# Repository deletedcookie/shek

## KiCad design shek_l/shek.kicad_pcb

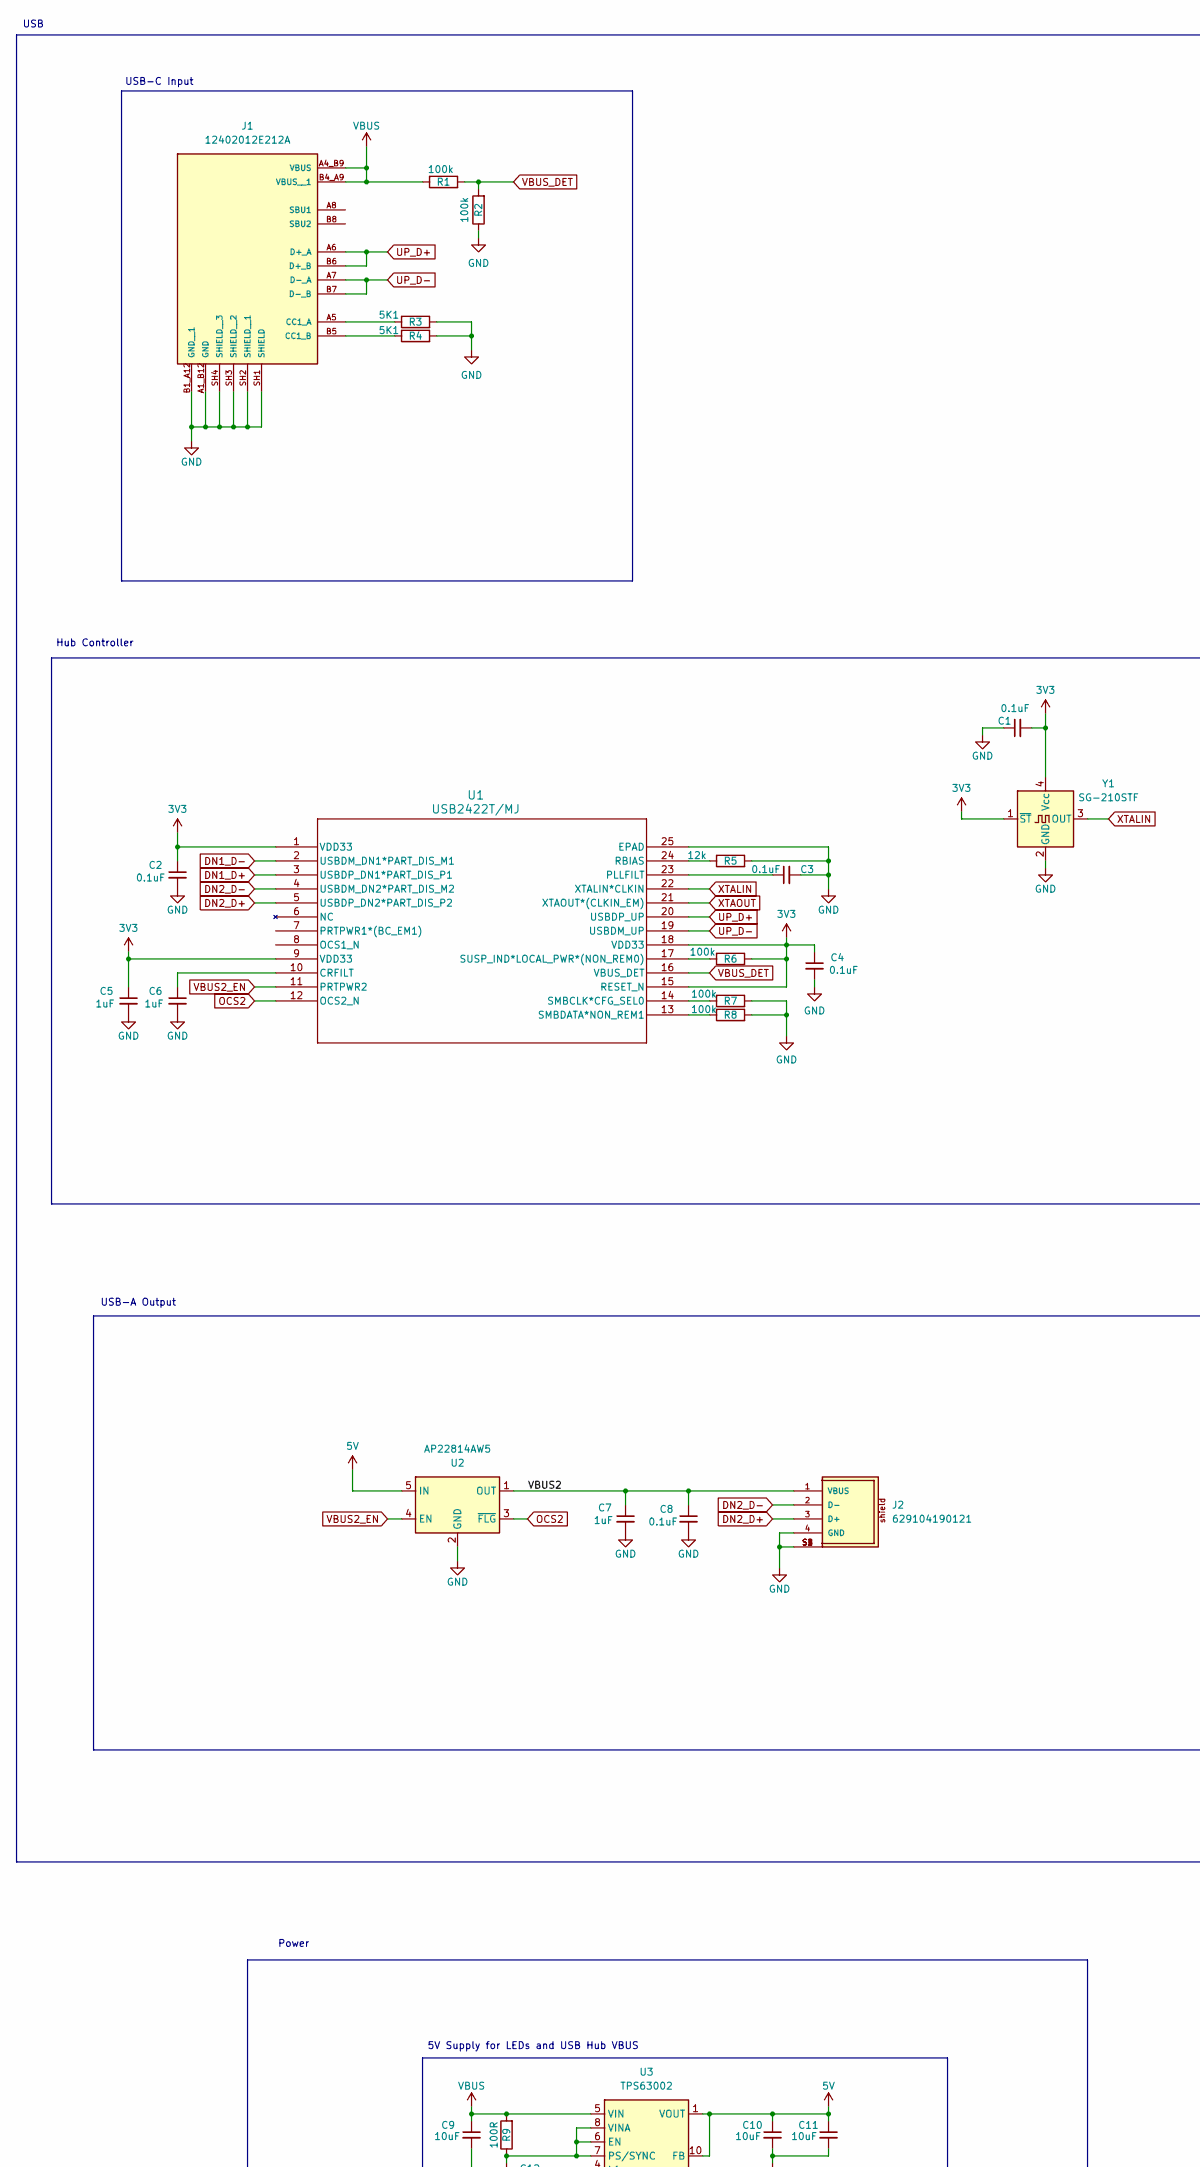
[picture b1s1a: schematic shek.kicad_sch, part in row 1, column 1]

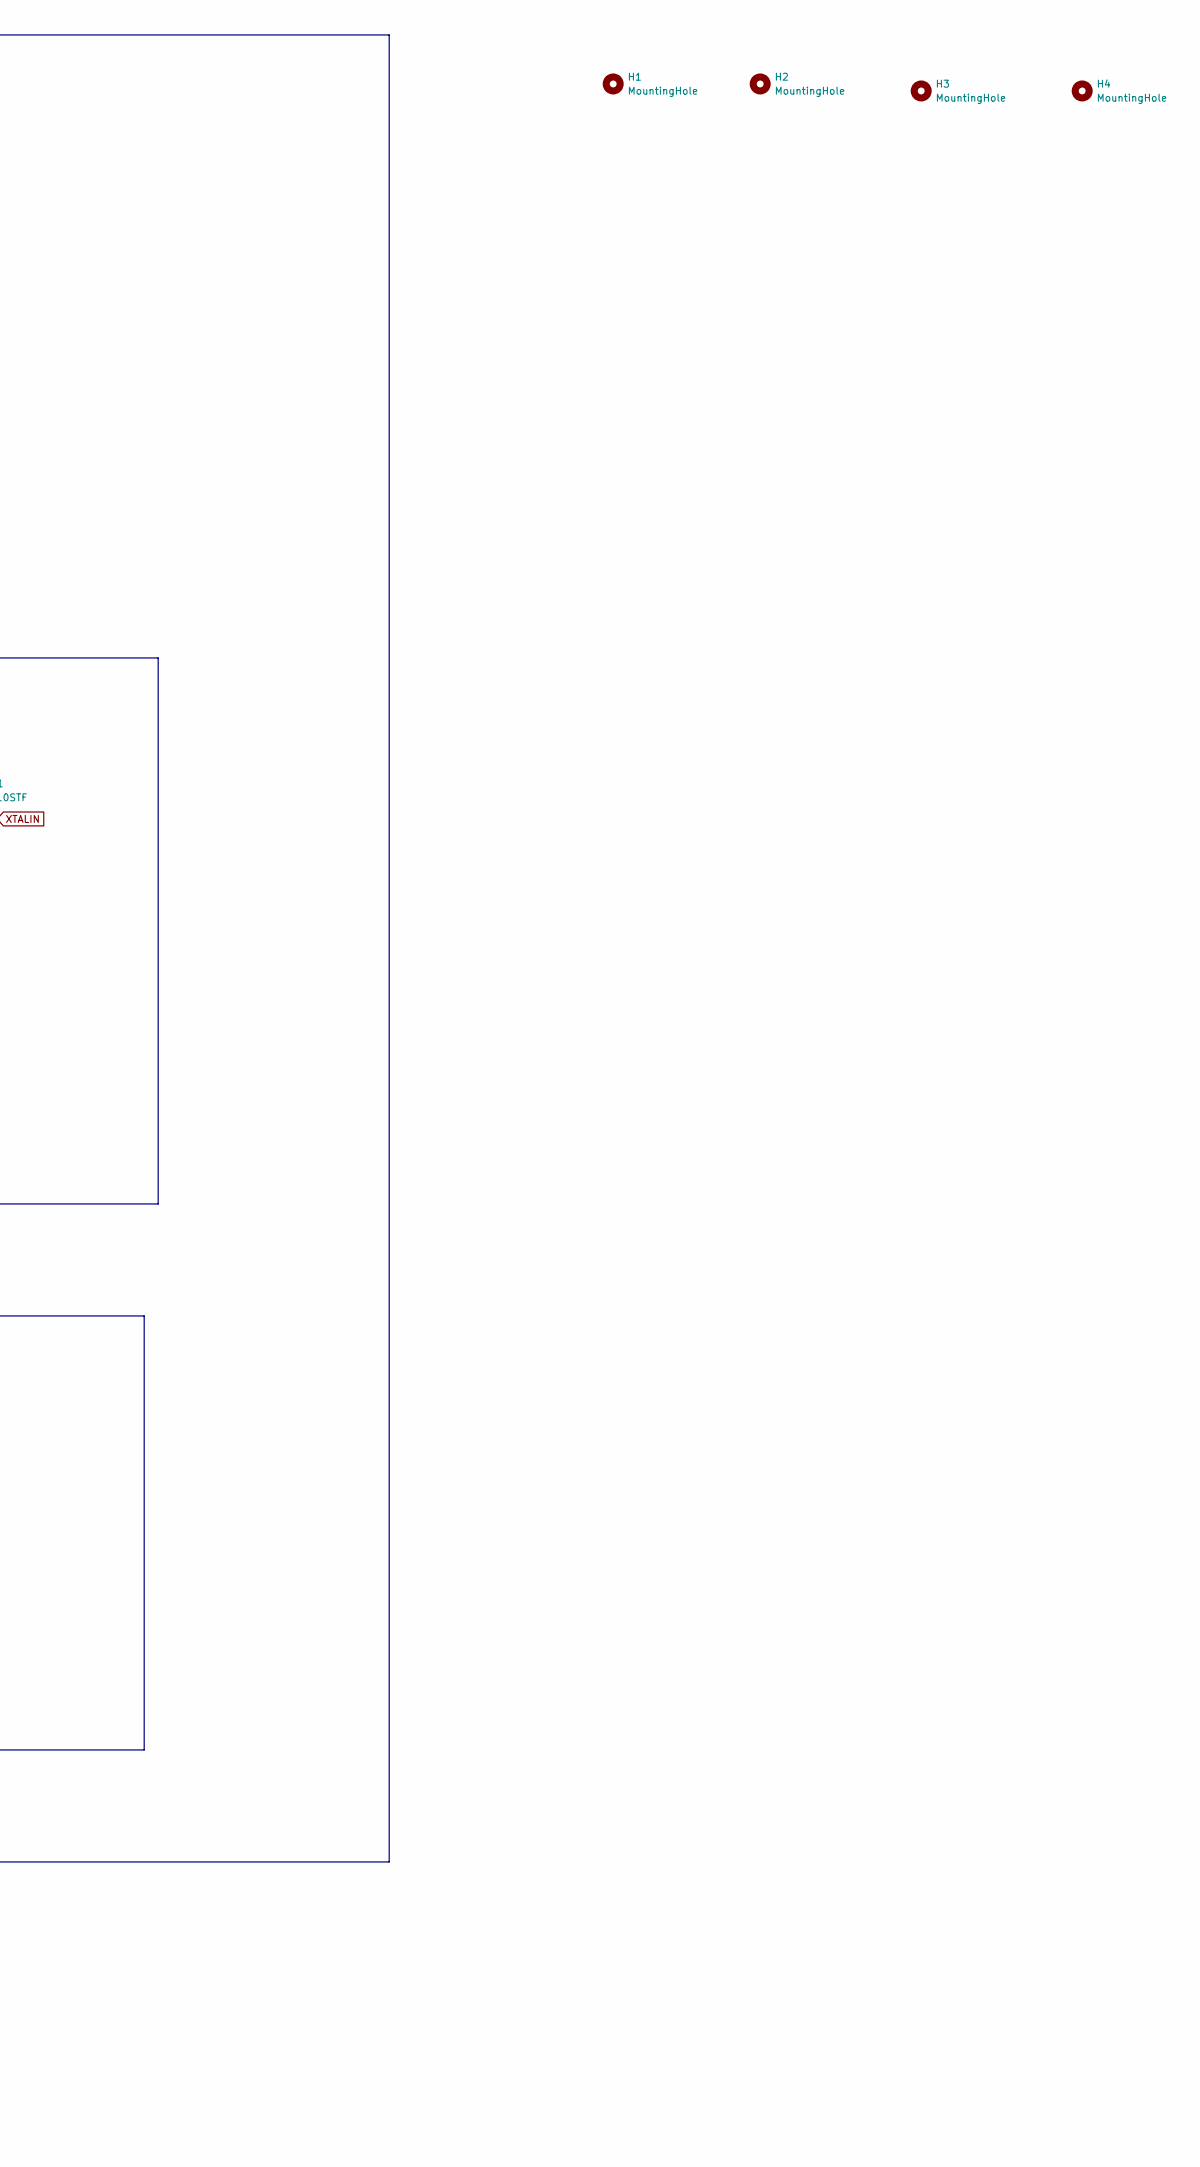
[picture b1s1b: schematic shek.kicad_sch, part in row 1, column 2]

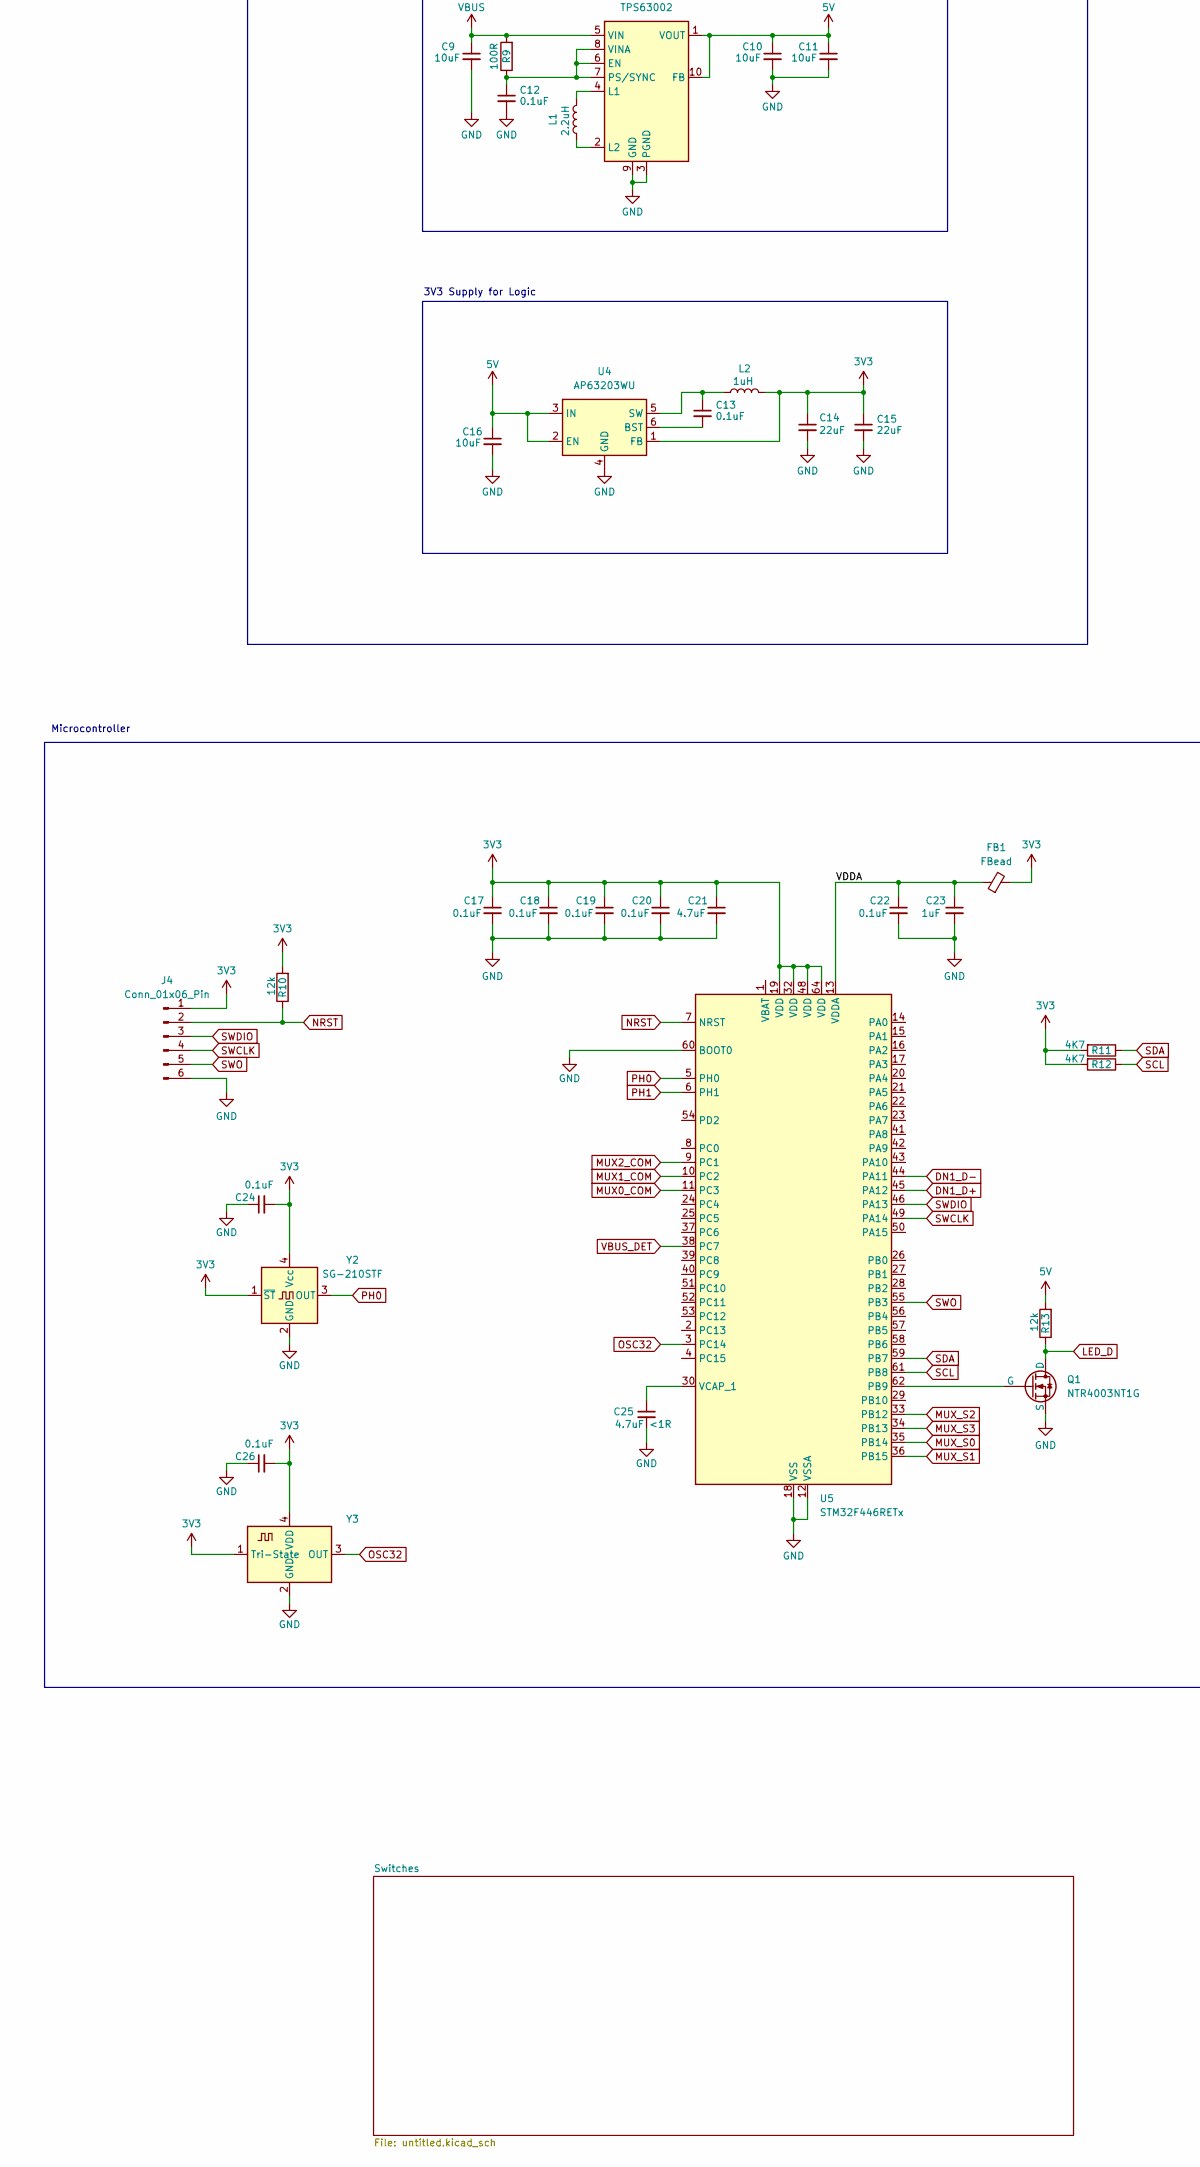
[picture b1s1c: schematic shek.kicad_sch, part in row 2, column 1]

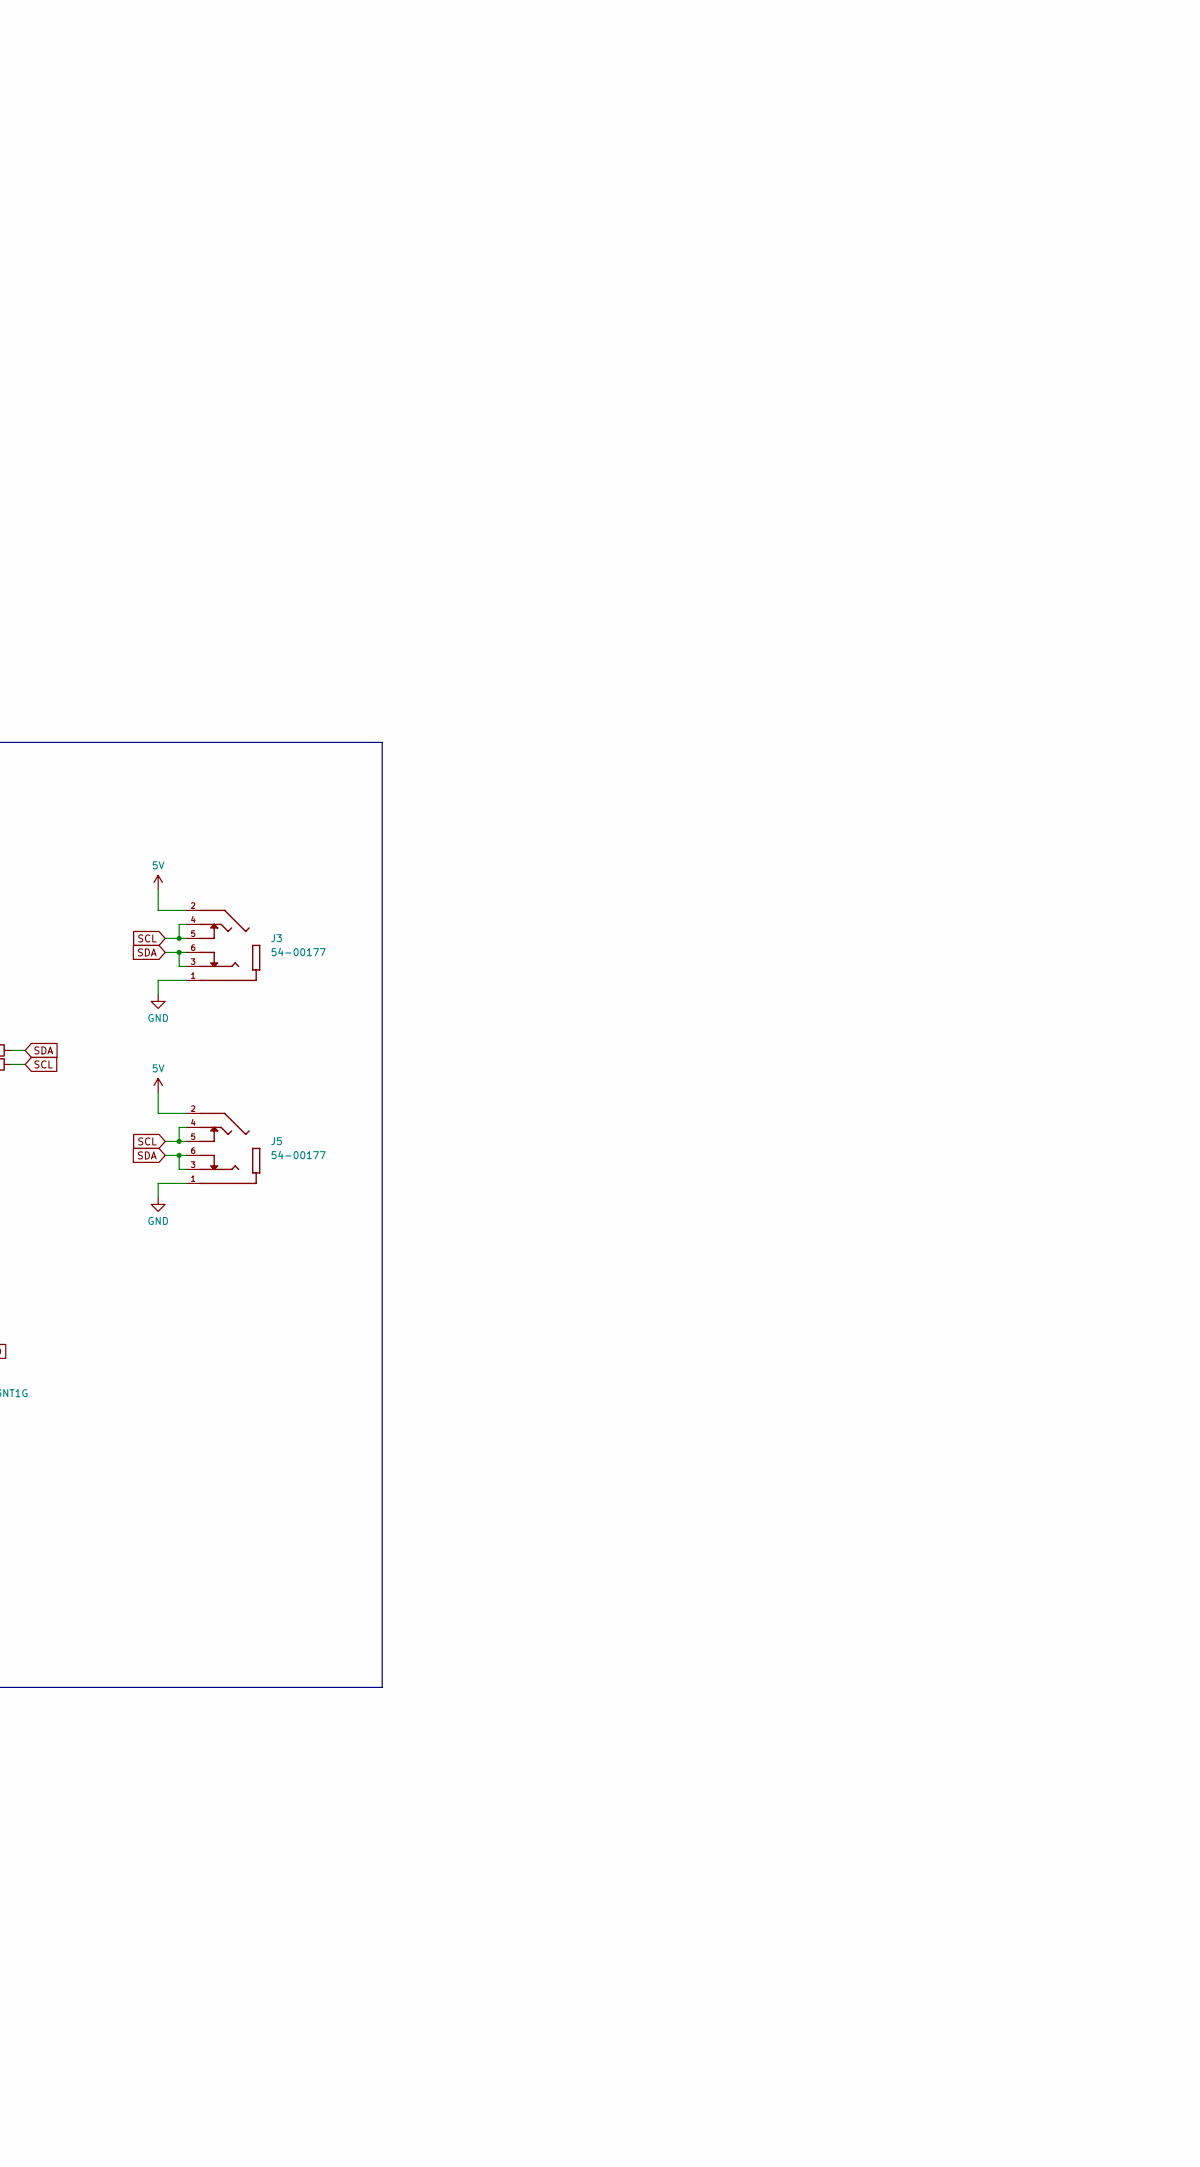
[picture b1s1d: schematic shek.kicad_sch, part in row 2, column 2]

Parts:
C1, C2, C3, C4, C8, C12, C13, C17, C18, C19, C20, C22, C24, C26: 0.1uF; C_0603_1608Metric; Digikey 311-1088-1-ND
C5, C6, C7, C23: 1uF; C_0603_1608Metric; Digikey 311-1445-1-ND
C9, C10, C11, C16: 10uF; C_0603_1608Metric; Digikey 311-1817-1-ND
C14, C15: 22uF; C_0603_1608Metric; Digikey 490-10476-1-ND
C21: 4.7uF; C_0603_1608Metric; Digikey 311-1785-1-ND
C25: 4.7uF <1R; C_0603_1608Metric; Digikey 311-1785-1-ND
FB1: FBead; L_0603_1608Metric; Digikey 240-2558-1-ND
H1, H2, H3, H4: MountingHole; MountingHole_3.2mm_M3
J1: 12402012E212A; AMPHENOL_12402012E212A; PARTREV 4; Digikey 664-12402012E212ACT-ND
J2: 629104190121
J3, J5: 54-00177; TENSILITY_54-00177; PARTREV A; Digikey 839-54-00177CT-ND
J4: Conn_01x06_Pin; PinHeader_1x06_P2.00mm_Horizontal
L1: 2.2uH; L_1008_2520Metric; Digikey 490-13055-1-ND
L2: 1uH; L_1008_2520Metric; Digikey 490-13053-1-ND
Q1: NTR4003NT1G; SOT-23-3; Digikey NTR4003NT1GOSCT-ND
R1, R2, R6, R7, R8: 100k; R_0603_1608Metric; Digikey RG16P100KBCT-ND
R3, R4: 5K1; R_0603_1608Metric; Digikey RG16P5.1KBCT-ND
R5, R10, R13: 12k; R_0603_1608Metric; Digikey RG16P12.0KBCT-ND
R9: 100R; R_0603_1608Metric; Digikey RG16P100BCT-ND
R11, R12: 4K7; R_0603_1608Metric; Digikey RG16P4.7KBCT-ND
U1: USB2422T/MJ; HVQFN-24-1EP_4x4mm_P0.5mm_EP2.5x2.5mm; Digikey USB2422T/MJCT-ND
U2: AP22814AW5; SOT-23-5; Digikey AP22814AW5-7DICT-ND
U3: TPS63002; Texas_DRC0010J; Digikey 296-19644-1-ND
U4: AP63203WU; TSOT-23-6; Digikey AP63203WU-7DICT-ND
U5: STM32F446RETx; LQFP-64_10x10mm_P0.5mm; Digikey 497-STM32F446RET6TRCT-ND
Y1, Y2: SG-210STF; Oscillator_SMD_SeikoEpson_SG210-4Pin_2.5x2.0mm; Digikey SER4078CT-ND
Y3: ASCO; Crystal_SMD_Abracon_ABM8G-4Pin_3.2x2.5mm_silkmod; Digikey 535-ASEK-32.768KHZ-L-R-TCT-ND

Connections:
3V3: C1.2, C2.1, C4.1, C5.1, C14.1, C15.1, C17.1, C18.1, C19.1, C20.1, C21.1, C24.2, C26.2, FB1.2, J4.1, L2.2, R6.1, R10.2, R11.2, R12.2, U1.1 (VDD33), U1.9 (VDD33), U1.15 (RESET_N), U1.18 (VDD33), U4.1 (FB), U5.19 (VDD), U5.32 (VDD), U5.48 (VDD), U5.64 (VDD), Y1.1 (~ST), Y1.4 (Vcc), Y2.1 (~ST), Y2.4 (Vcc), Y3.1 (Tri-State), Y3.4 (VDD); also elsewhere on the board
5V: C10.1, C11.1, C16.1, J3.2, J5.2, R13.2, U2.5 (IN), U3.1 (VOUT), U3.10 (FB), U4.2 (EN), U4.3 (IN); also elsewhere on the board
/VBUS2: C7.1, C8.1, J2.1 (VBUS), U2.1 (OUT)
/VDDA: C22.1, C23.1, FB1.1, U5.13 (VDDA)
DN1_D+: U1.3 (USBDP_DN1*PART_DIS_P1), U5.45 (PA12)
DN1_D-: U1.2 (USBDM_DN1*PART_DIS_M1), U5.44 (PA11)
DN2_D+: J2.3 (D+), U1.5 (USBDP_DN2*PART_DIS_P2)
DN2_D-: J2.2 (D-), U1.4 (USBDM_DN2*PART_DIS_M2)
GND: C1.1, C2.2, C3.2, C4.2, C5.2, C6.2, C7.2, C8.2, C9.2, C10.2, C11.2, C12.2, C14.2, C15.2, C16.2, C17.2, C18.2, C19.2, C20.2, C21.2, C22.2, C23.2, C24.1, C25.2, C26.1, J1.A1_B12 (GND), J1.B1_A12 (GND__1), J1.SH1 (SHIELD), J1.SH2 (SHIELD__1), J1.SH3 (SHIELD__2), J1.SH4 (SHIELD__3), J2.4 (GND), J2.S1, J2.S2, J2.S3, J2.S4, J3.1, J4.6, J5.1, Q1.2 (S), R2.1, R3.2, R4.2, R5.2, R7.2, R8.2, U1.25 (EPAD), U2.2 (GND), U3.3 (PGND), U3.9 (GND), U3.11 (PGND), U4.4 (GND), U5.12 (VSSA), U5.18 (VSS), U5.31 (VSS), U5.47 (VSS), U5.60 (BOOT0), U5.63 (VSS), Y1.2 (GND), Y2.2 (GND), Y3.2 (GND); also elsewhere on the board
LED_D: Q1.3 (D), R13.1; also elsewhere on the board
MUX0_COM: U5.11 (PC3); also elsewhere on the board
MUX1_COM: U5.10 (PC2); also elsewhere on the board
MUX2_COM: U5.9 (PC1); also elsewhere on the board
MUX_S0: U5.35 (PB14); also elsewhere on the board
MUX_S1: U5.36 (PB15); also elsewhere on the board
MUX_S2: U5.33 (PB12); also elsewhere on the board
MUX_S3: U5.34 (PB13); also elsewhere on the board
NRST: J4.2, R10.1, U5.7 (NRST)
unnamed: J1.A5 (CC1_A), R3.1
unnamed: J1.B5 (CC1_B), R4.1
unnamed: Q1.1 (G), U5.62 (PB9)
unnamed: C6.1, U1.10 (CRFILT)
unnamed: C3.1, U1.23 (PLLFILT)
unnamed: R5.1, U1.24 (RBIAS)
unnamed: R7.1, U1.14 (SMBCLK*CFG_SEL0)
unnamed: R8.1, U1.13 (SMBDATA*NON_REM1)
unnamed: R6.2, U1.17 (SUSP_IND*LOCAL_PWR*(NON_REM0))
unnamed: C12.1, R9.1, U3.6 (EN), U3.7 (PS/SYNC), U3.8 (VINA)
unnamed: L1.2, U3.4 (L1)
unnamed: L1.1, U3.2 (L2)
unnamed: C13.2, U4.6 (BST)
unnamed: C13.1, L2.1, U4.5 (SW)
unnamed: C25.1, U5.30 (VCAP_1)
OCS2: U1.12 (OCS2_N), U2.3 (~FLG)
OSC32: U5.3 (PC14), Y3.3 (OUT)
PH0: U5.5 (PH0), Y2.3 (OUT)
PH1: U5.6 (PH1)
SCL: J3.4, J3.5, J5.4, J5.5, R12.1, U5.61 (PB8)
SDA: J3.3, J3.6, J5.3, J5.6, R11.1, U5.59 (PB7)
SWCLK: J4.4, U5.49 (PA14)
SWDIO: J4.3, U5.46 (PA13)
SWO: J4.5, U5.55 (PB3)
UP_D+: J1.A6 (D+_A), J1.B6 (D+_B), U1.20 (USBDP_UP)
UP_D-: J1.A7 (D-_A), J1.B7 (D-_B), U1.19 (USBDM_UP)
VBUS: C9.1, J1.A4_B9 (VBUS), J1.B4_A9 (VBUS__1), R1.1, R9.2, U3.5 (VIN)
VBUS2_EN: U1.11 (PRTPWR2), U2.4 (EN)
VBUS_DET: R1.2, R2.2, U1.16 (VBUS_DET), U5.38 (PC7)
XTALIN: U1.22 (XTALIN*CLKIN), Y1.3 (OUT)
XTAOUT: U1.21 (XTAOUT*(CLKIN_EM))

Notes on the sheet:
USB
USB-A Output
Microcontroller
3V3 Supply for Logic
Power
5V Supply for LEDs and USB Hub VBUS
USB-C Input
Hub Controller
